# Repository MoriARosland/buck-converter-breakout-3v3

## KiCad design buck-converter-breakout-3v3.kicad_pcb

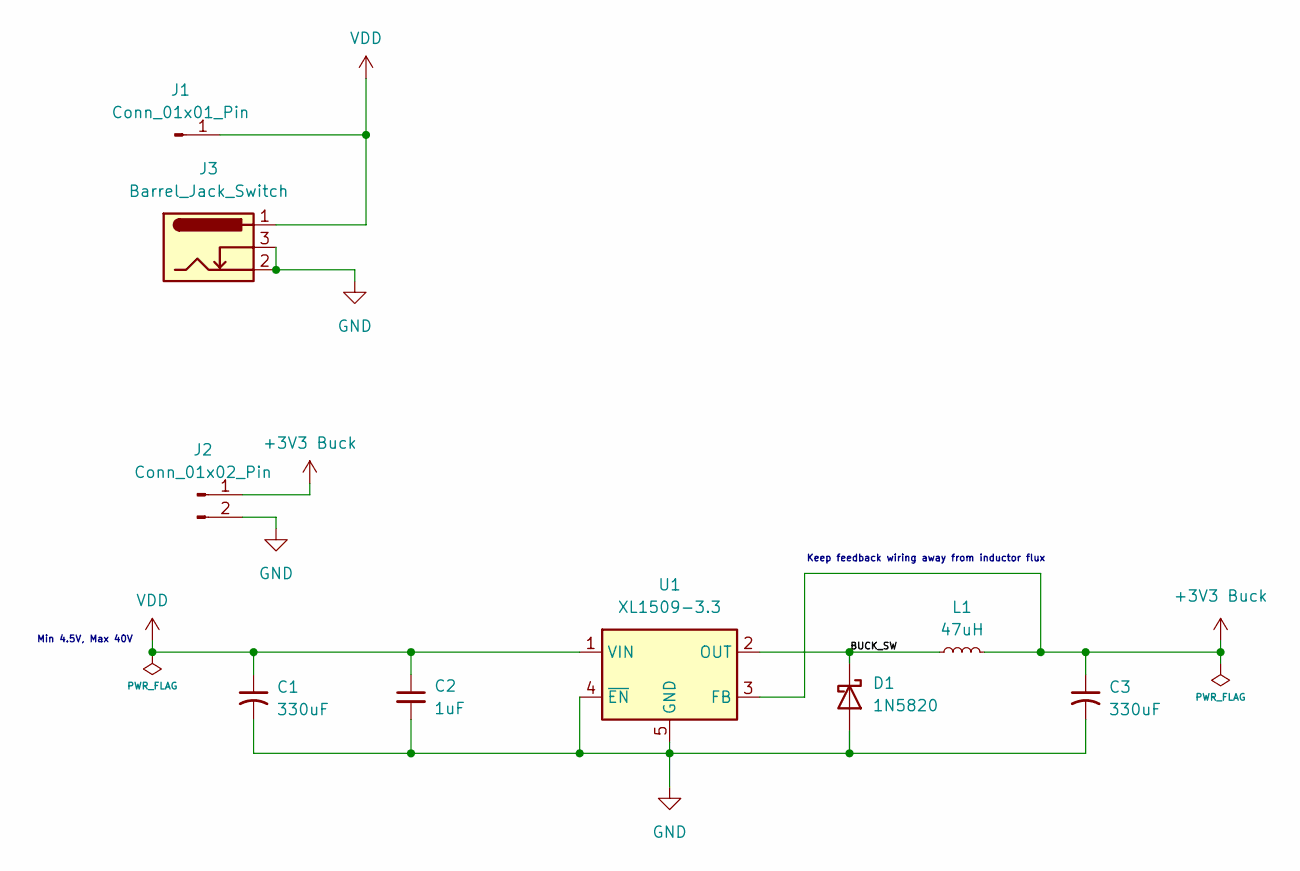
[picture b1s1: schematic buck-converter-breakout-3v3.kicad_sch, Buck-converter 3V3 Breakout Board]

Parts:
C1, C3: 330uF; CP_Radial_D10.0mm_P5.00mm; LCSC Part # C45107
C2: 1uF; C_0603_1608Metric_Pad1.08x0.95mm_HandSolder; LCSC Part # C15849
D1: 1N5820; D_DO-201AD_P12.70mm_Horizontal; LCSC Part # C95400
J1: Conn_01x01_Pin; PinHeader_1x01_P2.54mm_Vertical; LCSC Part # C492400
J2: Conn_01x02_Pin; PinHeader_1x02_P2.54mm_Vertical; LCSC Part # C124375
J3: Barrel_Jack_Switch; BarrelJack_CUI_PJ-102AH_Horizontal; LCSC Part # C3096093
L1: 47uH; L_Chilisin_BMRF00101040; LCSC Part # C6364681
U1: XL1509-3.3; SOIC-8_3.9x4.9mm_P1.27mm; LCSC Part # C2681226

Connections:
+3V3 Buck: C3.1, J2.1, L1.2, U1.3 (FB)
/BUCK_SW: D1.1 (K), L1.1, U1.2 (OUT)
GND: C1.2, C2.2, C3.2, D1.2 (A), J2.2, J3.2, J3.3, U1.4 (~EN), U1.5 (GND), U1.6 (GND), U1.7 (GND), U1.8 (GND)
VDD: C1.1, C2.1, J1.1, J3.1, U1.1 (VIN)

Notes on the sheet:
Keep feedback wiring away from inductor flux
Min 4.5V, Max 40V

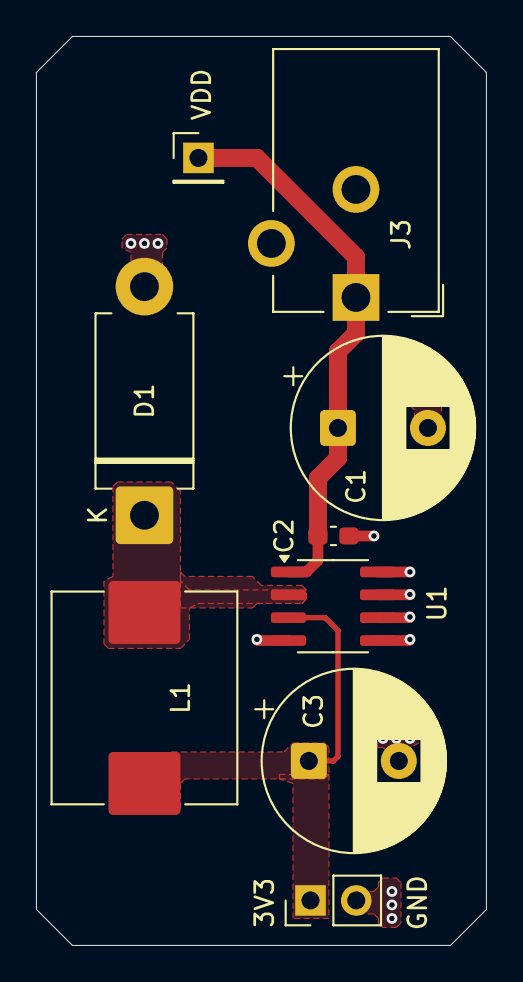
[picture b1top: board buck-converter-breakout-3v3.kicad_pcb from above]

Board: 2 copper layers, 25.0 x 50.5 mm, 9 parts (0 on the bottom side), 4 nets.

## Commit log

2025-08-20 initial kicad files
2025-08-21 feat: XL1509-3.3 buck-converter schematic
2025-08-24 feat: footprint lib and 3d models
2025-08-24 feat: component selection
2025-10-14 feat: layout and routing
2025-10-18 rework layout
2025-10-19 finalize layout
2025-10-19 rename project
2025-10-19 ignore production files
